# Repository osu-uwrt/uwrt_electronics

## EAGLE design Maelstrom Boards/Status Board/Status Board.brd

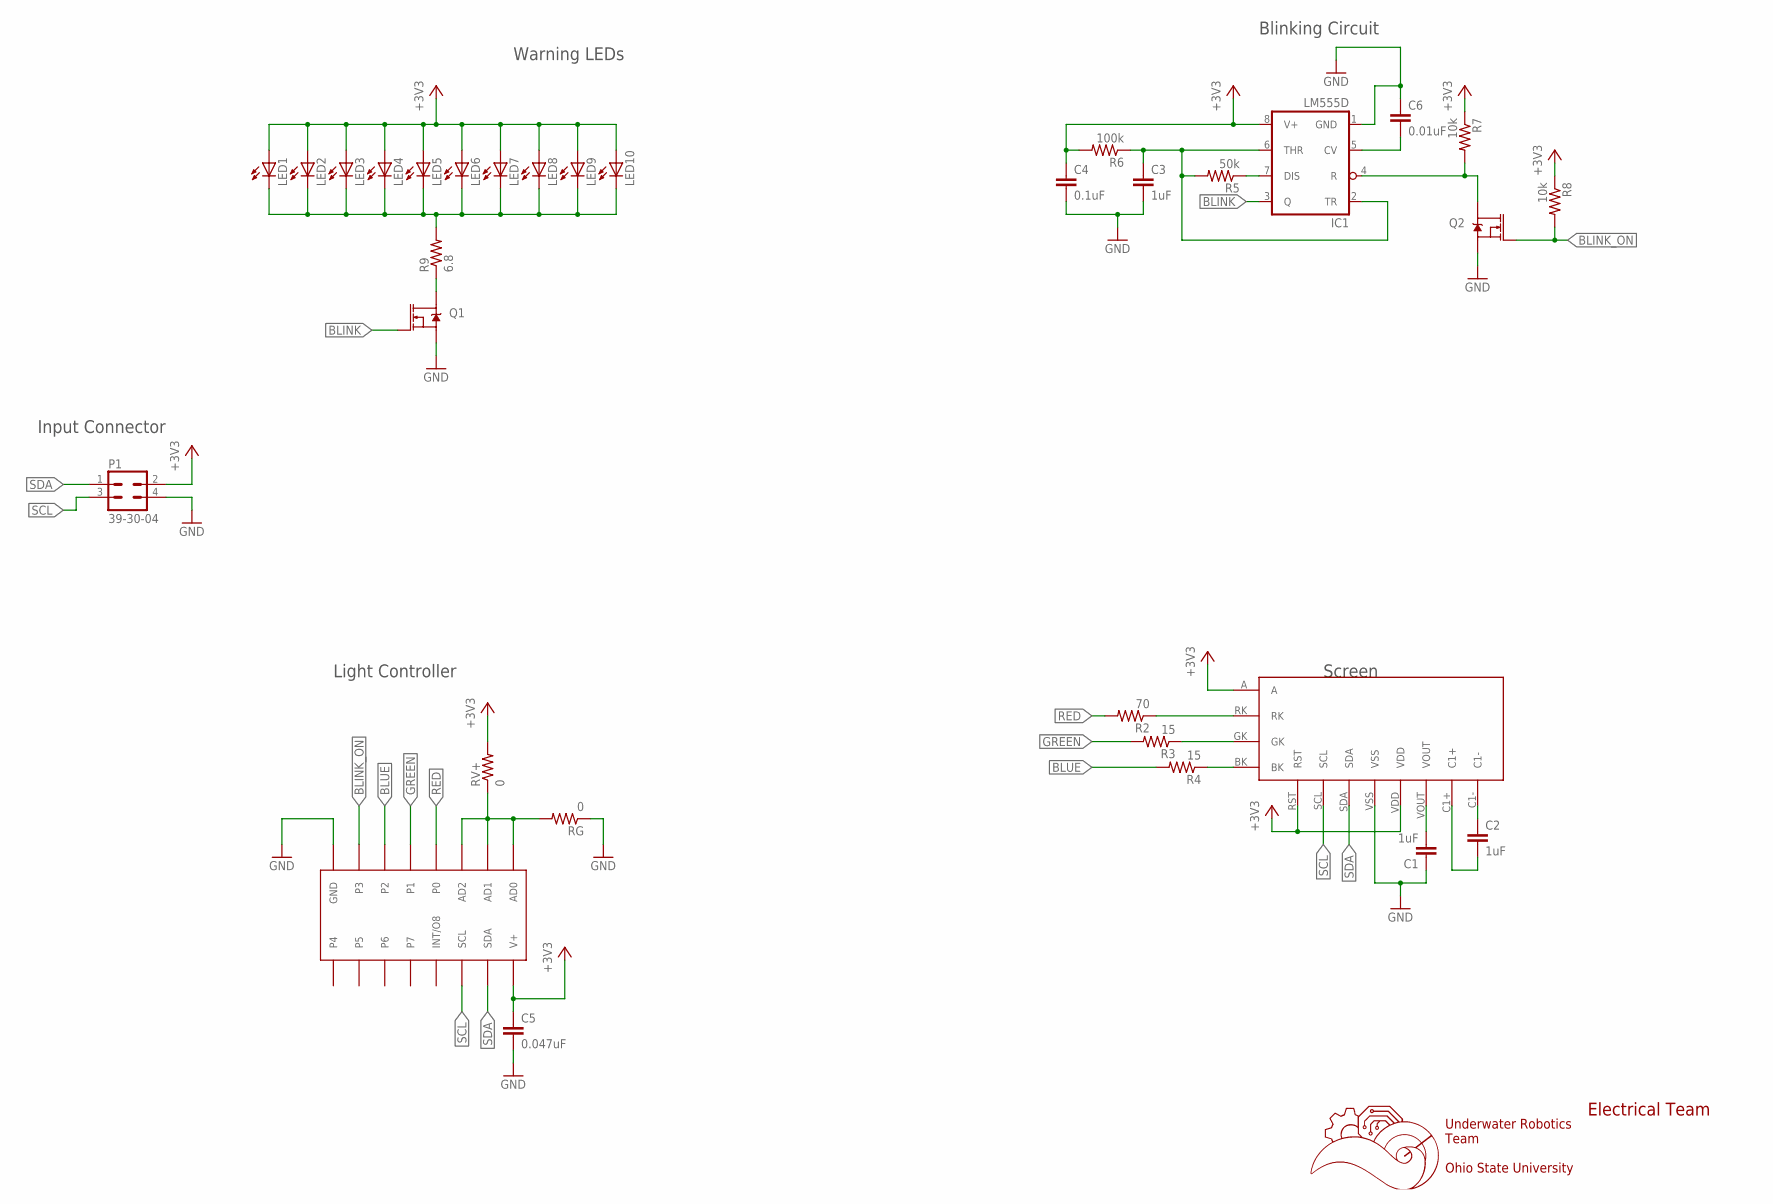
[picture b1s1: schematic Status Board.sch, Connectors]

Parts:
C1, C2, C3: 1uF; C0603
C4: 0.1uF; C0603
C5: 0.047uF; C0603
C6: 0.01uF; C0603
IC1: LM555D; SO08
LED1, LED2, LED3, LED4, LED5, LED6, LED7, LED8, LED9, LED10: LEDCHIPLED_0603; CHIPLED_0603
P1: 39-30-04; 39-30-?04?
Q1, Q2: 310mA/60V/1.6Ω; SOT323
R2: 70; R0603
R3, R4: 15; R0603
R5: 50k; R0603
R6: 100k; R0603
R7, R8: 10k; R0603
R9: 6.8; R0603
RG: 0; R0603
RV+: 0; R0603
U$1: NHD-C0220BIZ
U$2: MAX7315; TSSOP-16

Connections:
+3V3: C4.1, C5.1, IC1.8 (V+), LED1.A, LED2.A, LED3.A, LED4.A, LED5.A, LED6.A, LED7.A, LED8.A, LED9.A, LED10.A, P1.2, R6.2, R7.1, R8.1, RV+.2, U$1.A, U$1.RST, U$1.VDD, U$2.16 (V+)
BLINK: IC1.3 (Q), Q1.1 (G)
BLINK_OFF: IC1.4 (R), Q2.3 (D), R7.2
BLINK_ON: Q2.1 (G), R8.2, U$2.7 (P3)
BLUE: R4.2, U$2.6 (P2)
GND: C1.1, C3.2, C4.2, C5.2, C6.1, IC1.1 (GND), P1.4, Q1.2 (S), Q2.2 (S), RG.1, U$1.VSS, U$2.8 (GND)
GREEN: R3.2, U$2.5 (P1)
unnamed: R3.1, U$1.GK
unnamed: C2.1, U$1.C1-
unnamed: C1.2, U$1.VOUT
unnamed: C2.2, U$1.C1+
unnamed: R4.1, U$1.BK
unnamed: RG.2, RV+.1, U$2.1 (AD0), U$2.2 (AD1), U$2.3 (AD2)
unnamed: R2.1, U$1.RK
unnamed: C6.2, IC1.5 (CV)
unnamed: IC1.7 (DIS), R5.1
unnamed: C3.1, IC1.2 (TR), IC1.6 (THR), R5.2, R6.1
unnamed: Q1.3 (D), R9.1
unnamed: LED1.C, LED2.C, LED3.C, LED4.C, LED5.C, LED6.C, LED7.C, LED8.C, LED9.C, LED10.C, R9.2
RED: R2.2, U$2.4 (P0)
SCL: P1.3, U$1.SCL, U$2.14 (SCL)
SDA: P1.1, U$1.SDA, U$2.15 (SDA)

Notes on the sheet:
Underwater Robotics Team Ohio State University
Electrical Team
Warning LEDs
Blinking Circuit
Screen
Light Controller
Input Connector

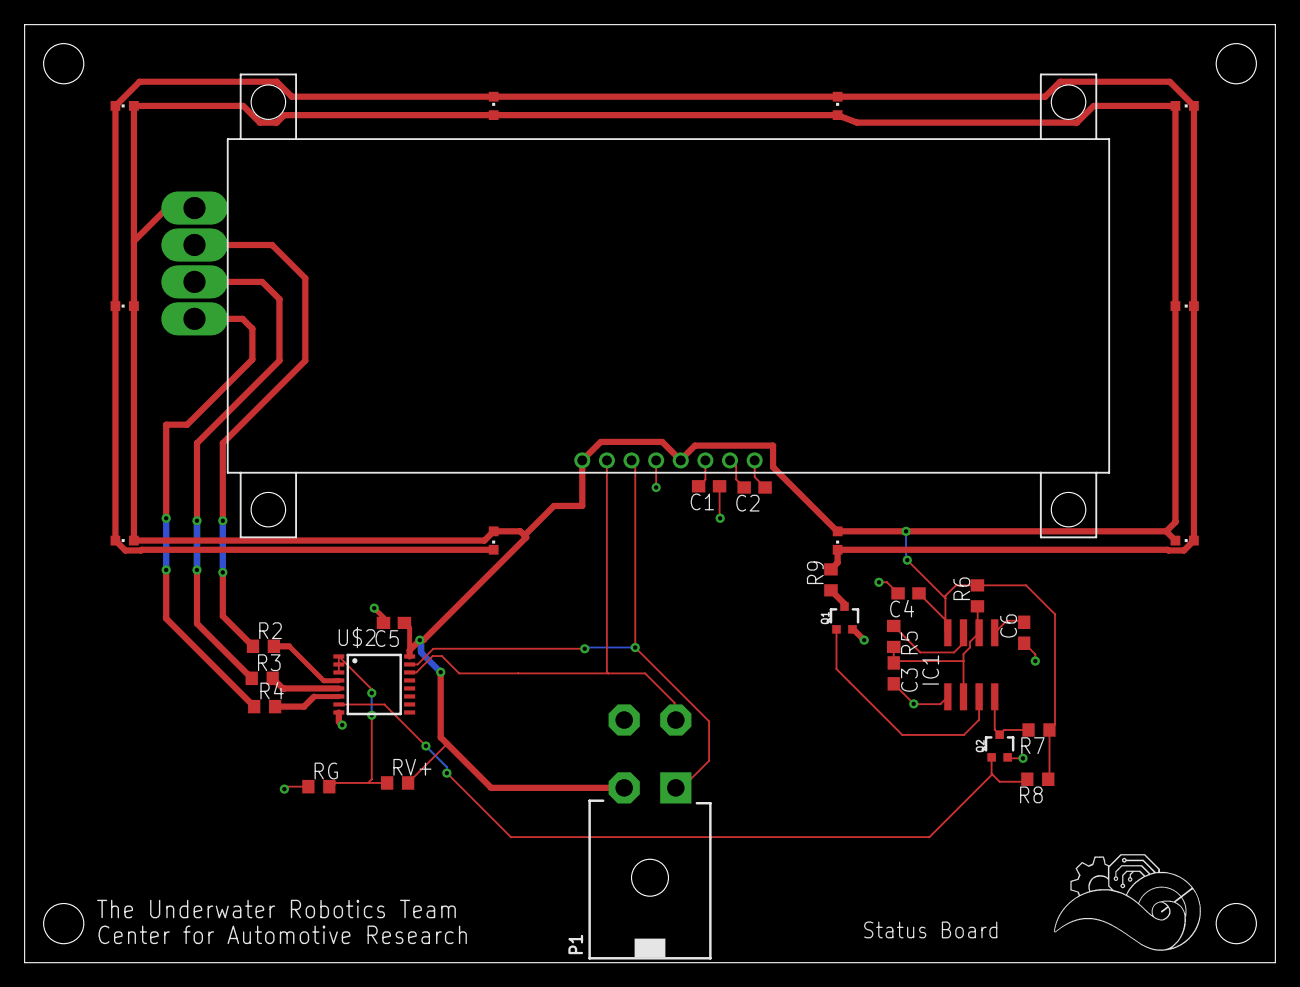
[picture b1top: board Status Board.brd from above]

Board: 2 copper layers, 101.6 x 76.2 mm, 32 parts (0 on the bottom side), 22 nets.

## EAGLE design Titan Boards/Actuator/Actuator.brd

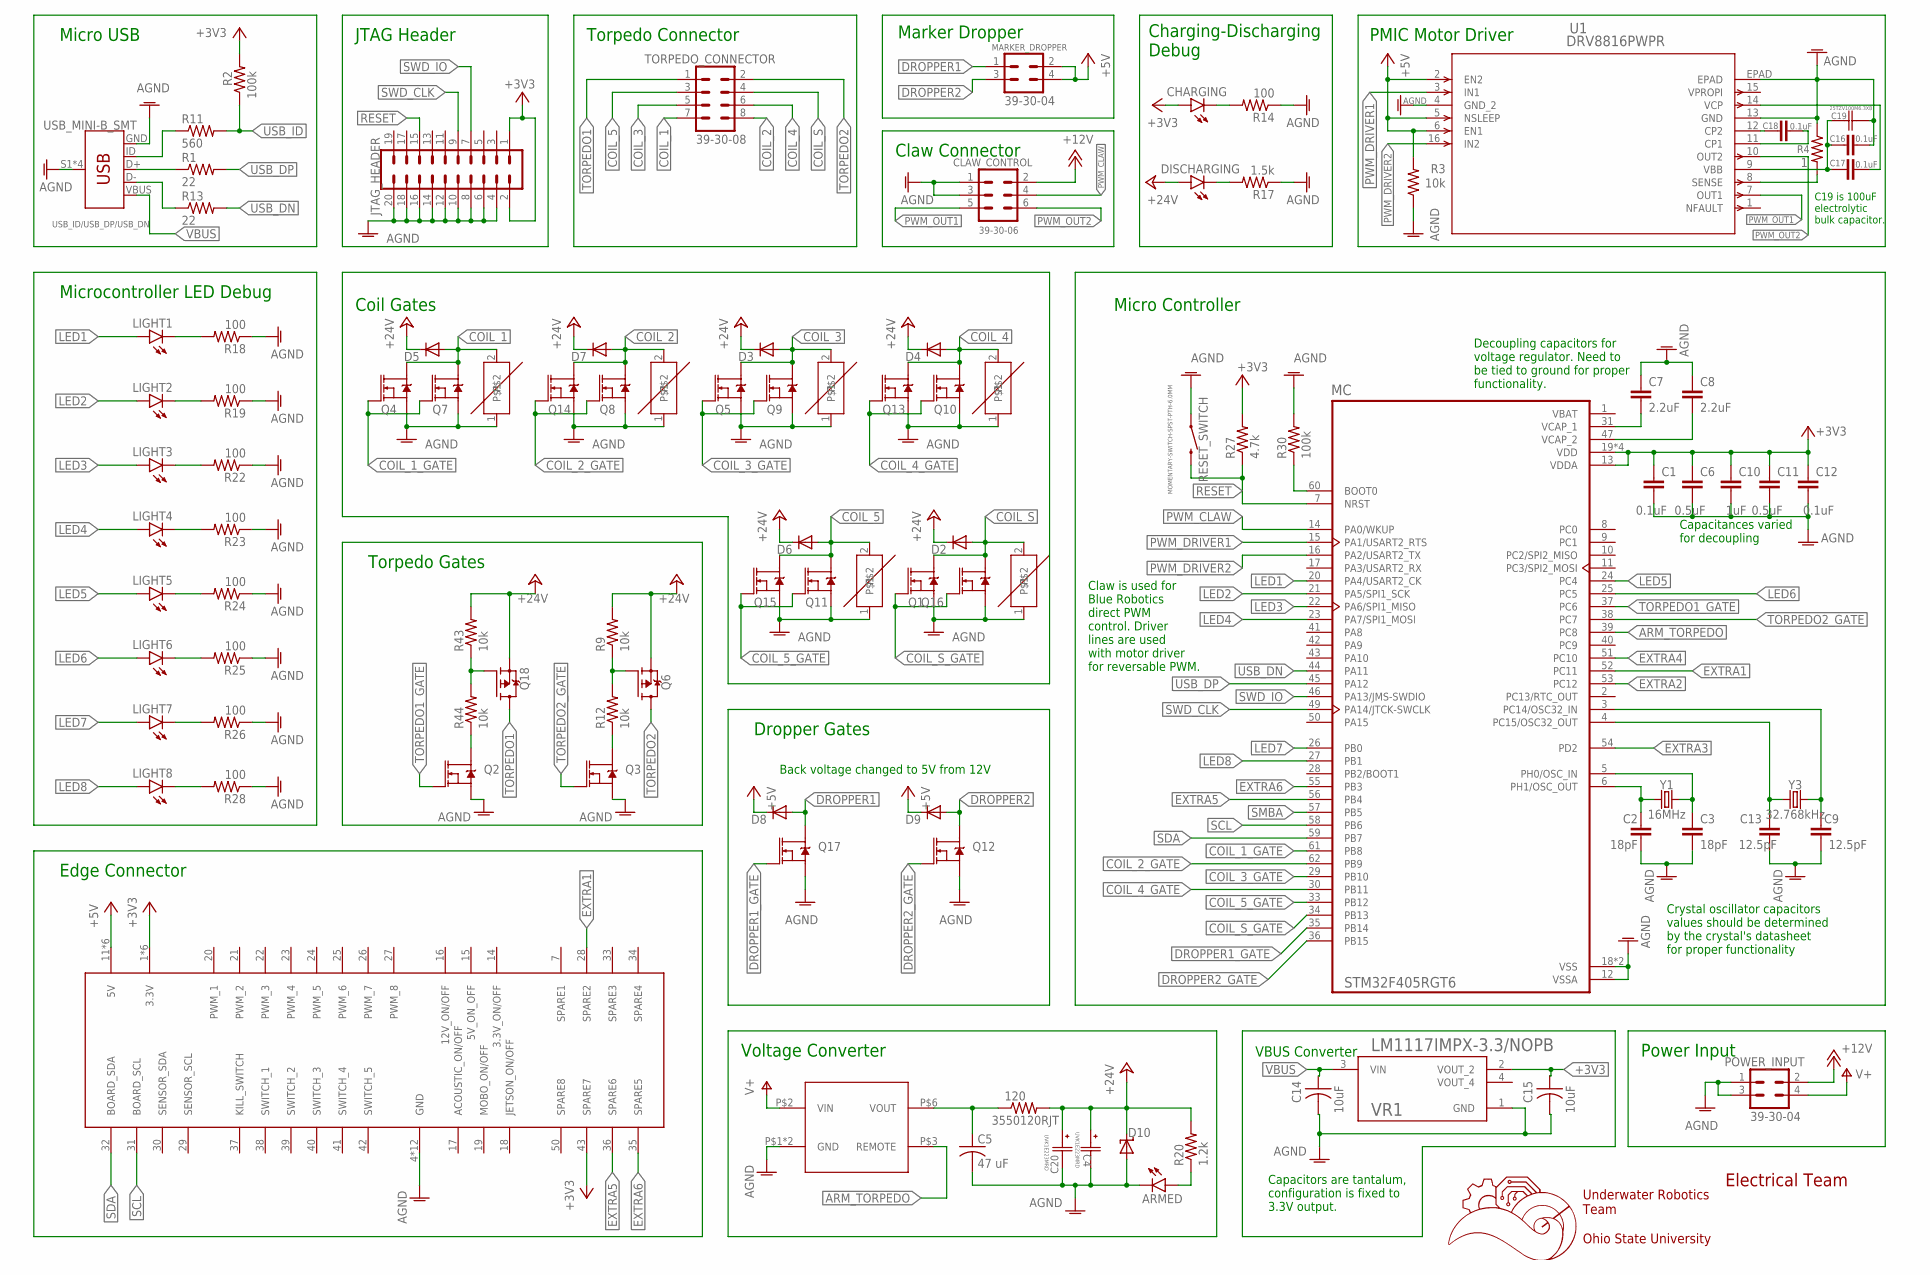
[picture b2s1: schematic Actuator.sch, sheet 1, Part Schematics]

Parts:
120: 3550120RJT
ARMED: LEDCHIPLED_0603; CHIPLED_0603
C1, C12, C16, C17, C18: 0.1uF; C0603
C2, C3: 18pF; C0603
C4, C20: UVK1E223MRD; CAP_UFW_25X50_NCH
C5: 47 uF; C1206K
C6, C11: 0.5uF; C0603
C7, C8: 2.2uF; C0603
C9, C13: 12.5pF; C0603
C10: 1uF; C0603
C14, C15: 10uF; C0603
C19: 25TZV100M6.3X8; CAP_J-V_6P3X8_RUB
CHARGING: LEDCHIPLED_0603; CHIPLED_0603
CLAW_CONTROL: 39-30-06; 39-30-?06?
D2, D3, D4, D5, D6, D7, D8, D9: DIODE-SMB; SMB
D10: SUPPRESSOR-SMBJ; SMBJ
DISCHARGING: LEDCHIPLED_0603; CHIPLED_0603
JTAG_HEADER: CONN_10X2; 2X10
LIGHT1, LIGHT2, LIGHT3, LIGHT4, LIGHT5, LIGHT6, LIGHT7, LIGHT8: LEDCHIPLED_0603; CHIPLED_0603
MARKER_DROPPER: 39-30-04; 39-30-?04?
MC: STM32F405RGT6; QFP50P1200X1200X160-64N
POWER_INPUT: 39-30-04; 39-30-?04?
Q1, Q2, Q3, Q4, Q5, Q7, Q8, Q9, Q10, Q11, Q12, Q13, Q14, Q15, Q16, Q17: MOSFET-NCH-AO3404A; SOT23-3
Q6, Q18: FDD4141TO252; TO252
R1, R13: 22; R0603
R2, R30: 100k; R0603
R3, R9, R12, R43, R44: 10k; R0603
R4: 1; R0805
R11: 560; R0603
R14, R18, R19, R22, R23, R24, R25, R26, R28: 100; R0805
R17: 1.5k; R0805
R20: 1.2k; R0805
R27: 4.7k; R0603
RESET_SWITCH: MOMENTARY-SWITCH-SPST-PTH-6.0MM; TACTILE_SWITCH_PTH_6.0MM
TORPEDO_CONNECTOR: 39-30-08; 39-30-?08?
U1: DRV8816PWPR; PWP_16
U$1: 5530843-EDGE; 5530843-6-BOARDFINGERS
U$2, U$3, U$4, U$5, U$7, U$8: ERZ-VF2M270ERZ-VF2M270; RESM8060X320N
U$6: TMR6-2415
USB_ID/USB_DP/USB_DN: USB_MINI-B_SMT; USB-MINIB
VR1: LM1117IMPX-3.3/NOPB; VREG_LM1117IMPX-3.3/NOPB
Y1: 16MHz; HC49US
Y3: 32.768kHz; CRYSTAL-SMD-3.2X1.5MM

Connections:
+3V3: C1.1, C6.1, C10.1, C11.1, C12.1, C15.1, CHARGING.A, JTAG_HEADER.1, JTAG_HEADER.2, MC.13 (VDDA), MC.19 (VDD), MC.32 (VDD), MC.48 (VDD), MC.64 (VDD), R2.2, R27.2, U$1.1 (3.3V), U$1.2 (3.3V), U$1.3 (3.3V), U$1.43 (SPARE7), U$1.54 (3.3V), U$1.55 (3.3V), U$1.56 (3.3V), VR1.2 (VOUT_2)
+5V: D8.C, D9.C, MARKER_DROPPER.2, MARKER_DROPPER.4, R3.2, U1.2 (EN2), U1.5 (NSLEEP), U1.6 (EN1), U$1.11 (5V), U$1.12 (5V), U$1.13 (5V), U$1.44 (5V), U$1.45 (5V), U$1.46 (5V)
+12V: CLAW_CONTROL.2, POWER_INPUT.2
+24V: 120.P$2 (2), C4.1, C20.1, D2.C, D3.C, D4.C, D5.C, D6.C, D7.C, D10.C, DISCHARGING.A, Q6.2 (S), Q18.2 (S), R9.2, R20.2, R43.2
AGND: ARMED.C, C1.2, C2.2, C3.2, C4.2, C5.2, C6.2, C7.1, C8.1, C9.2, C10.2, C11.2, C12.2, C13.2, C14.2, C15.2, C16.2, C19.2, C20.2, CLAW_CONTROL.1, CLAW_CONTROL.3, D10.A, JTAG_HEADER.4, JTAG_HEADER.6, JTAG_HEADER.8, JTAG_HEADER.10, JTAG_HEADER.12, JTAG_HEADER.14, JTAG_HEADER.16, JTAG_HEADER.18, JTAG_HEADER.20, MC.12 (VSSA), MC.18 (VSS), MC.63 (VSS), POWER_INPUT.1, POWER_INPUT.3, Q1.2 (S), Q2.2 (S), Q3.2 (S), Q4.2 (S), Q5.2 (S), Q7.2 (S), Q8.2 (S), Q9.2 (S), Q10.2 (S), Q11.2 (S), Q12.2 (S), Q13.2 (S), Q14.2 (S), Q15.2 (S), Q16.2 (S), Q17.2 (S), R3.1, R4.1, R14.1, R17.1, R18.1, R19.1, R22.1, R23.1, R24.1, R25.1, R26.1, R28.1, R30.2, RESET_SWITCH.1, U1.4 (GND_2), U1.13 (GND), U1.EPAD, U$1.4 (GND), U$1.5 (GND), U$1.6 (GND), U$1.8 (GND), U$1.9 (GND), U$1.10 (GND), U$1.47 (GND), U$1.48 (GND), U$1.49 (GND), U$1.51 (GND), U$1.52 (GND), U$1.53 (GND), U$2.1, U$3.1, U$4.1, U$5.1, U$6.P$1 (GND), U$6.P$7 (GND), U$7.1, U$8.1, USB_ID/USB_DP/USB_DN.GND, USB_ID/USB_DP/USB_DN.S1 (SHIELD), USB_ID/USB_DP/USB_DN.S2 (SHIELD), USB_ID/USB_DP/USB_DN.S3 (SHIELD), USB_ID/USB_DP/USB_DN.S4 (SHIELD), VR1.1 (GND)
ARM_TORPEDO: MC.39 (PC8), U$6.P$3 (REMOTE)
COIL_1: D5.A, Q4.3 (D), Q7.3 (D), TORPEDO_CONNECTOR.7, U$8.2
COIL_1_GATE: MC.61 (PB8), Q4.1 (G), Q7.1 (G)
COIL_2: D7.A, Q8.3 (D), Q14.3 (D), TORPEDO_CONNECTOR.8, U$7.2
COIL_2_GATE: MC.62 (PB9), Q8.1 (G), Q14.1 (G)
COIL_3: D3.A, Q5.3 (D), Q9.3 (D), TORPEDO_CONNECTOR.5, U$5.2
COIL_3_GATE: MC.29 (PB10), Q5.1 (G), Q9.1 (G)
COIL_4: D4.A, Q10.3 (D), Q13.3 (D), TORPEDO_CONNECTOR.6, U$4.2
COIL_4_GATE: MC.30 (PB11), Q10.1 (G), Q13.1 (G)
COIL_5: D6.A, Q11.3 (D), Q15.3 (D), TORPEDO_CONNECTOR.3, U$3.2
COIL_5_GATE: MC.33 (PB12), Q11.1 (G), Q15.1 (G)
COIL_S: D2.A, Q1.3 (D), Q16.3 (D), TORPEDO_CONNECTOR.4, U$2.2
COIL_S_GATE: MC.34 (PB13), Q1.1 (G), Q16.1 (G)
DROPPER1: D8.A, MARKER_DROPPER.1, Q17.3 (D)
DROPPER1_GATE: MC.35 (PB14), Q17.1 (G)
DROPPER2: D9.A, MARKER_DROPPER.3, Q12.3 (D)
DROPPER2_GATE: MC.36 (PB15), Q12.1 (G)
EXTRA1: MC.52 (PC11), U$1.28 (SPARE2)
EXTRA2: MC.53 (PC12)
EXTRA3: MC.54 (PD2)
EXTRA4: MC.51 (PC10)
EXTRA5: MC.56 (PB4), U$1.36 (SPARE6)
EXTRA6: MC.55 (PB3), U$1.35 (SPARE5)
LED1: LIGHT1.A, MC.20 (PA4/USART2_CK)
LED2: LIGHT2.A, MC.21 (PA5/SPI1_SCK)
LED3: LIGHT3.A, MC.22 (PA6/SPI1_MISO)
LED4: LIGHT4.A, MC.23 (PA7/SPI1_MOSI)
LED5: LIGHT5.A, MC.24 (PC4)
LED6: LIGHT6.A, MC.25 (PC5)
LED7: LIGHT7.A, MC.26 (PB0)
LED8: LIGHT8.A, MC.27 (PB1)
unnamed: C2.1, MC.6 (PH1/OSC_OUT), Y1.1
unnamed: C3.1, MC.5 (PH0/OSC_IN), Y1.2
unnamed: CHARGING.C, R14.2
unnamed: C8.2, MC.47 (VCAP_2)
unnamed: R11.1, USB_ID/USB_DP/USB_DN.ID
unnamed: R1.1, USB_ID/USB_DP/USB_DN.D+
unnamed: R13.1, USB_ID/USB_DP/USB_DN.D-
unnamed: ARMED.A, R20.1
unnamed: C7.2, MC.31 (VCAP_1)
unnamed: C13.1, MC.4 (PC15/OSC32_OUT), Y3.P$2 (2)
unnamed: DISCHARGING.C, R17.2
unnamed: LIGHT1.C, R18.2
unnamed: LIGHT2.C, R19.2
unnamed: LIGHT3.C, R22.2
unnamed: LIGHT4.C, R23.2
unnamed: LIGHT5.C, R24.2
unnamed: LIGHT6.C, R25.2
unnamed: LIGHT7.C, R26.2
unnamed: LIGHT8.C, R28.2
unnamed: 120.P$1 (1), C5.1, U$6.P$6 (VOUT)
unnamed: C9.1, MC.3 (PC14/OSC32_IN), Y3.P$1 (1)
unnamed: MC.60 (BOOT0), R30.1
unnamed: Q18.1 (G), R43.1, R44.2
unnamed: Q2.3 (D), R44.1
unnamed: Q6.1 (G), R9.1, R12.2
unnamed: Q3.3 (D), R12.1
unnamed: R4.2, U1.8 (SENSE)
unnamed: C17.2, U1.14 (VCP)
unnamed: C16.1, C17.1, C19.1, U1.9 (VBB)
unnamed: C18.2, U1.11 (CP1)
unnamed: C18.1, U1.12 (CP2)
PWM_CLAW: CLAW_CONTROL.4, MC.14 (PA0/WKUP)
PWM_DRIVER1: MC.15 (PA1/USART2_RTS), U1.3 (IN1)
PWM_DRIVER2: MC.16 (PA2/USART2_TX), U1.16 (IN2)
PWM_OUT1: CLAW_CONTROL.5, U1.7 (OUT1)
PWM_OUT2: CLAW_CONTROL.6, U1.10 (OUT2)
RESET: JTAG_HEADER.15, MC.7 (NRST), R27.1, RESET_SWITCH.3 (2)
SCL: MC.58 (PB6), U$1.31 (BOARD_SCL)
SDA: MC.59 (PB7), U$1.32 (BOARD_SDA)
SMBA: MC.57 (PB5)
SWD_CLK: JTAG_HEADER.9, MC.49 (PA14/JTCK-SWCLK)
SWD_IO: JTAG_HEADER.7, MC.46 (PA13/JMS-SWDIO)
TORPEDO1: Q18.3 (D), TORPEDO_CONNECTOR.1
TORPEDO1_GATE: MC.37 (PC6), Q2.1 (G)
TORPEDO2: Q6.3 (D), TORPEDO_CONNECTOR.2
TORPEDO2_GATE: MC.38 (PC7), Q3.1 (G)
USB_DN: MC.44 (PA11), R13.2
USB_DP: MC.45 (PA12), R1.2
USB_ID: R2.1, R11.2
V+: POWER_INPUT.4, U$6.P$2 (VIN)
VBAT: MC.1 (VBAT)
VBUS: C14.1, USB_ID/USB_DP/USB_DN.VBUS, VR1.3 (VIN)

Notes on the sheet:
Underwater Robotics Team Ohio State University
Electrical Team
Micro USB
JTAG Header
Torpedo Connector
Claw Connector
Charging-Discharging Debug
Microcontroller LED Debug
Edge Connector
Voltage Converter
Decoupling capacitors for voltage regulator. Need to be tied to ground for proper functionality.
Crystal oscillator capacitors values should be determined by the crystal's datasheet for proper functionality
Dropper Gates
Coil Gates
Torpedo Gates
Marker Dropper
Power Input
Micro Controller
Back voltage changed to 5V from 12V
Capacitances varied for decoupling
Capacitors are tantalum, configuration is fixed to 3.3V output.
VBUS Converter
PMIC Motor Driver
Claw is used for Blue Robotics direct PWM control. Driver lines are used with motor driver for reversable PWM.
C19 is 100uF electrolytic bulk capacitor.

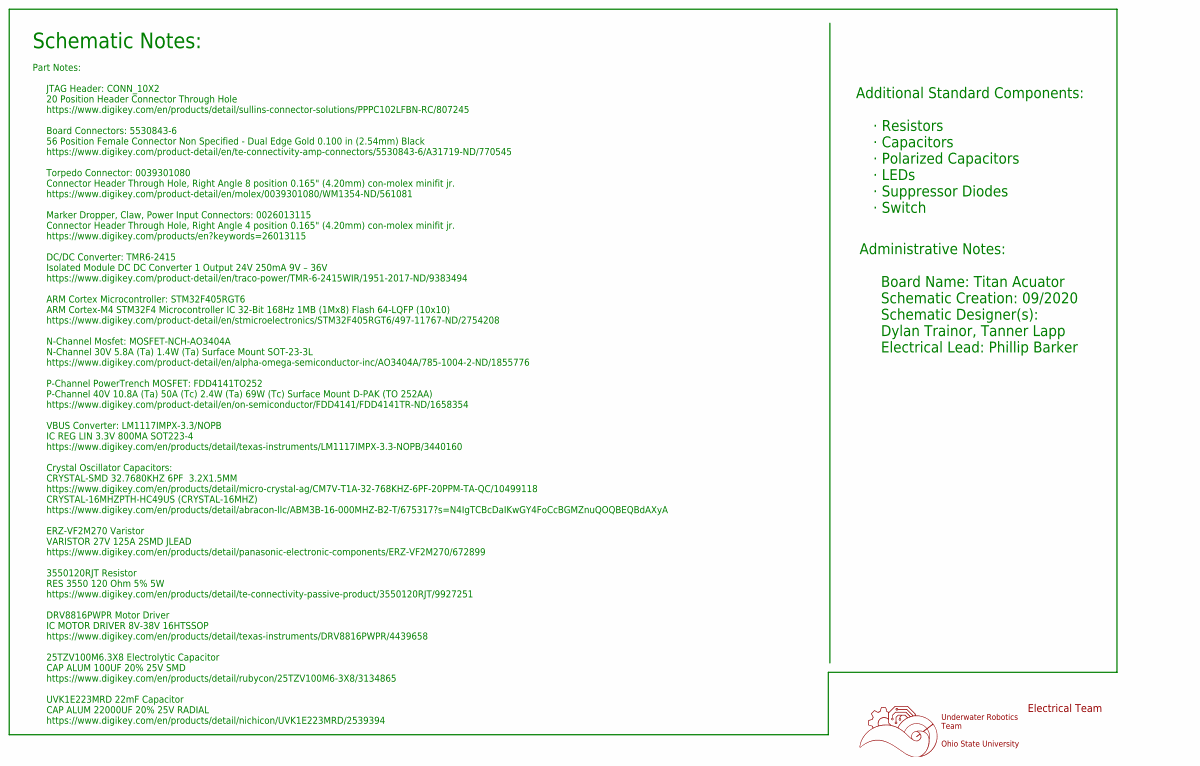
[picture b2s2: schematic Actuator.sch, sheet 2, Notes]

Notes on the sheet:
Underwater Robotics Team Ohio State University
Electrical Team
Schematic Notes:
Part Notes: JTAG Header: CONN_10X2 20 Position Header Connector Through Hole https://www.digikey.com/en/products/detail/sullins-connector-solutions/PPPC102LFBN-RC/807245 Board Connectors: 5530843-6 56 Position Female Connector Non Specified - Dual Edge Gold 0.100 in (2.54mm) Black https://www.digik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
Administrative Notes: Board Name: Titan Acuator Schematic Creation: 09/2020 Schematic Designer(s): Dylan Trainor, Tanner Lapp Electrical Lead: Phillip Barker
Additional Standard Components: · Resistors · Capacitors · Polarized Capacitors · LEDs · Suppressor Diodes · Switch

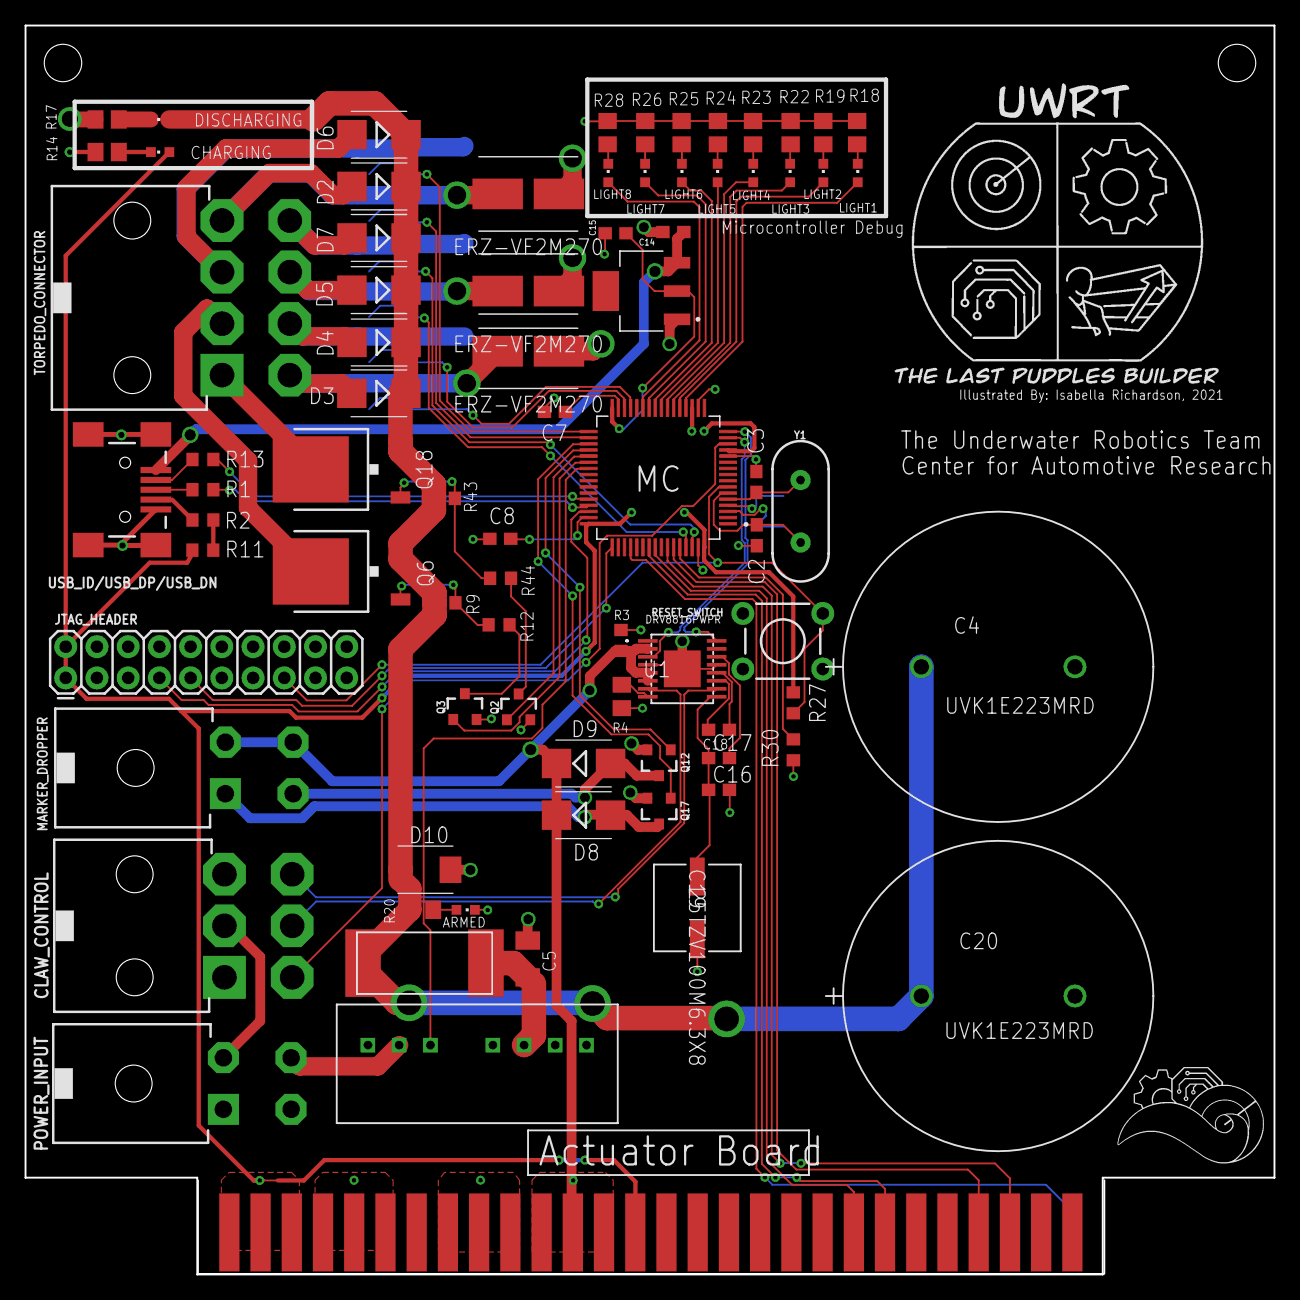
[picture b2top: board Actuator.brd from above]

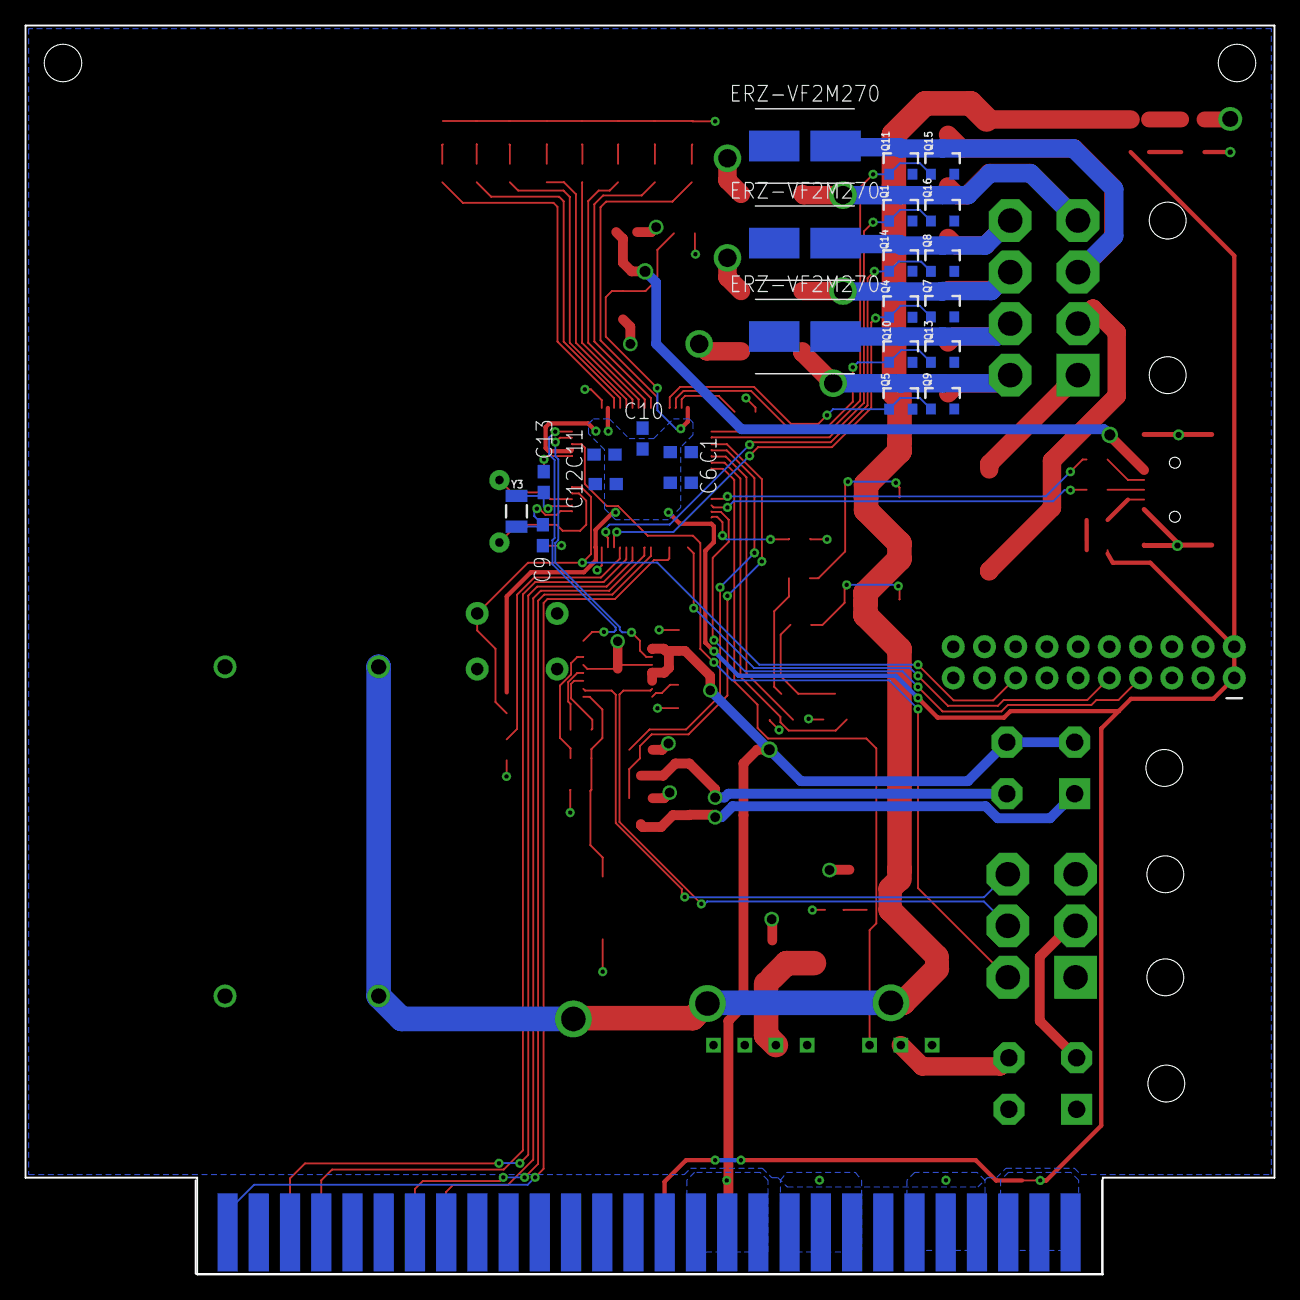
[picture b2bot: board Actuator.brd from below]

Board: 2 copper layers, 101.6 x 101.6 mm, 102 parts (23 on the bottom side), 83 nets.

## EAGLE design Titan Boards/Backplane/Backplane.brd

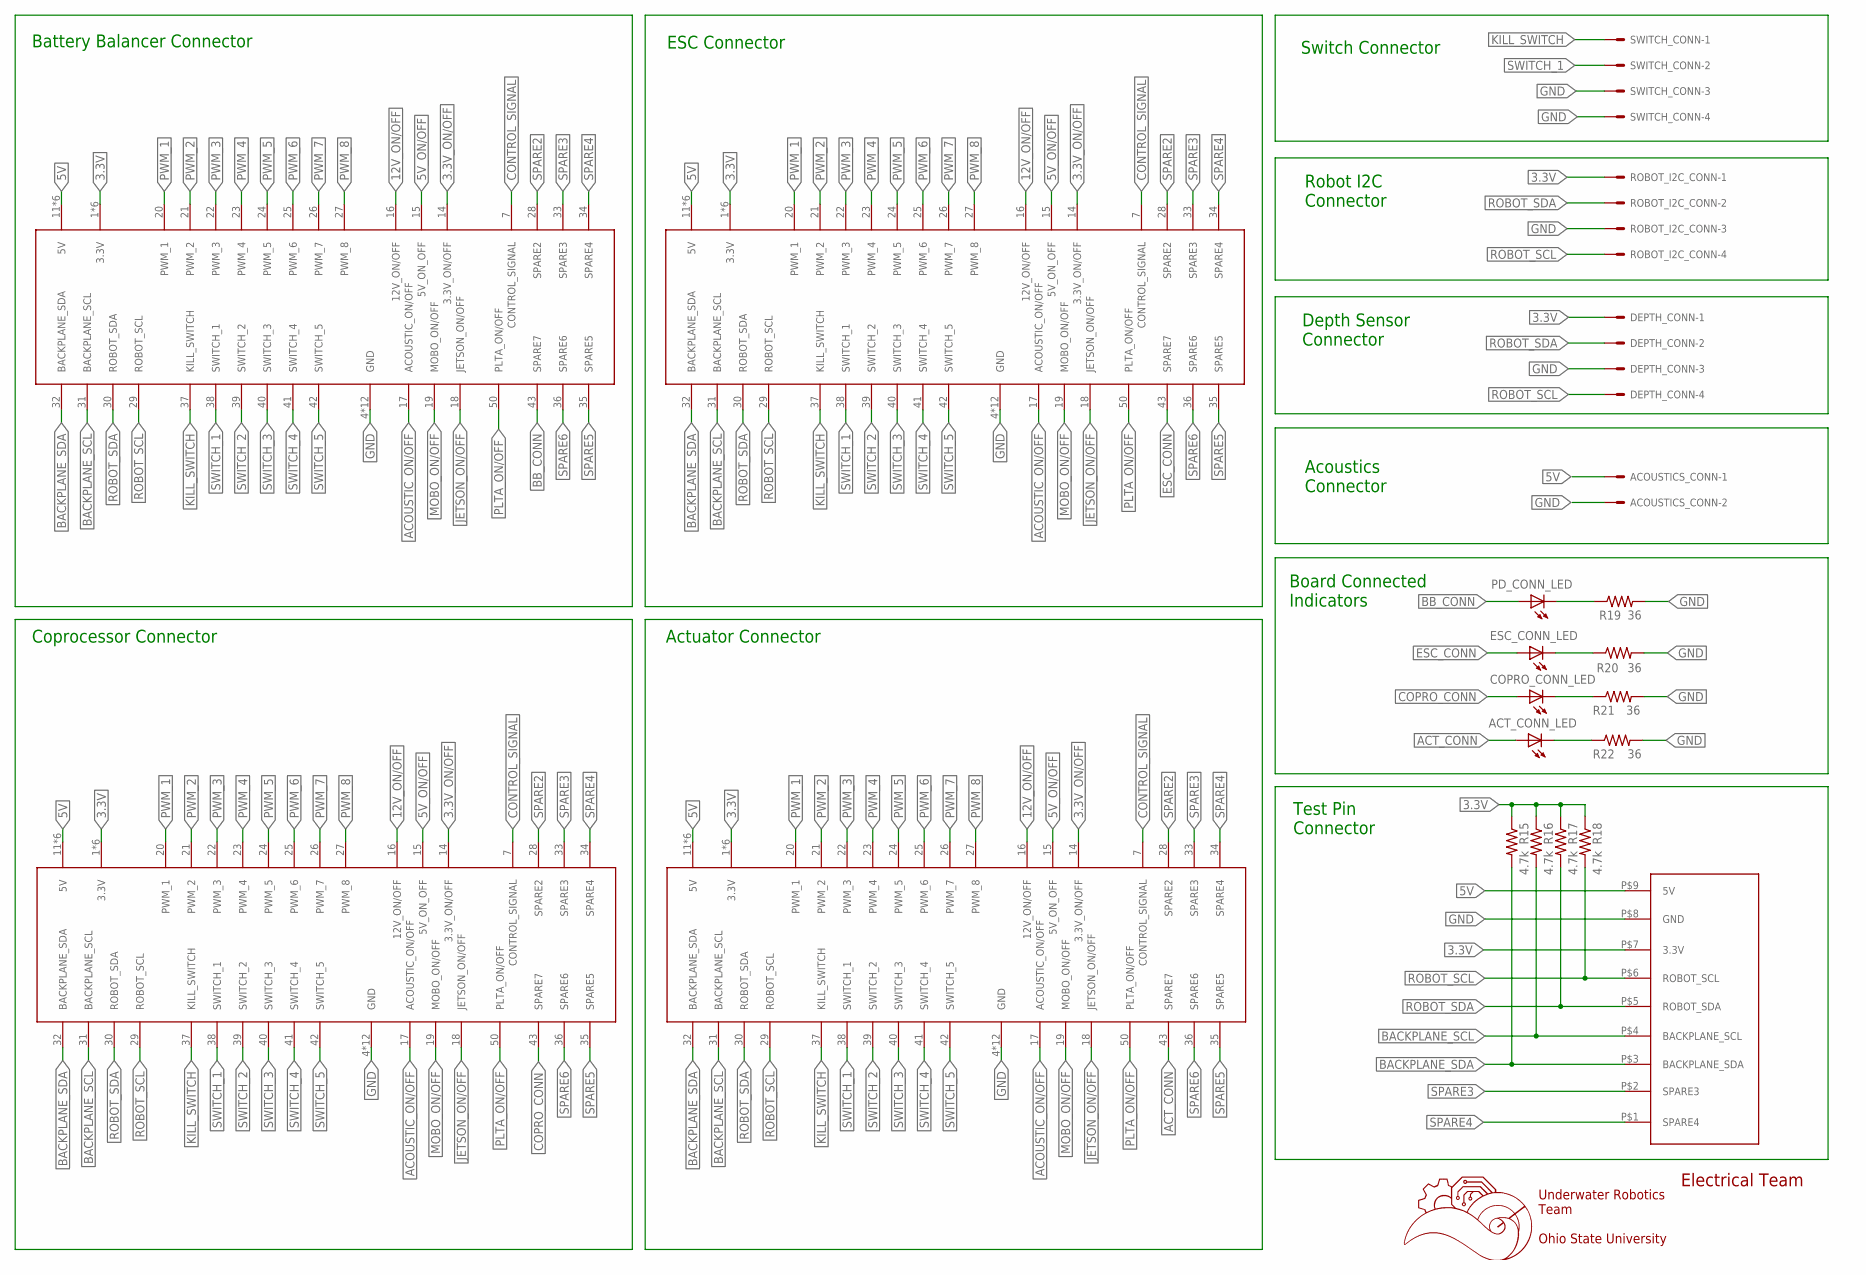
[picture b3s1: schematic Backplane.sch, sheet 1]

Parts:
ACOUSTICS_CONN: 555X-2V; 5566-2
ACT_CONN_LED: LEDCHIP-LED0603; CHIP-LED0603
COPRO_CONN_LED: LEDCHIP-LED0603; CHIP-LED0603
DEPTH_CONN: 555X-4V; 5566-4
ESC_CONN_LED: LEDCHIP-LED0603; CHIP-LED0603
PD_CONN_LED: LEDCHIP-LED0603; CHIP-LED0603
R15, R16, R17, R18: 4.7k; R0603
R19, R20, R21, R22: 36; R0603
ROBOT_I2C_CONN: 555X-4V; 5566-4
SWITCH_CONN: 555X-4V; 5566-4
TESTPIN_CONNECTOR: 929870-01-09_4; 929852-01-09_1ROW
U$1, U$2, U$3, U$4: 5530843-FEMALE; 5530843-6-BACKPLANEMATE

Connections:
3.3V: DEPTH_CONN.1, R15.1, R16.1, R17.1, R18.1, ROBOT_I2C_CONN.1, TESTPIN_CONNECTOR.P$7 (3.3V), U$1.1 (3.3V), U$1.2 (3.3V), U$1.3 (3.3V), U$1.54 (3.3V), U$1.55 (3.3V), U$1.56 (3.3V), U$2.1 (3.3V), U$2.2 (3.3V), U$2.3 (3.3V), U$2.54 (3.3V), U$2.55 (3.3V), U$2.56 (3.3V), U$3.1 (3.3V), U$3.2 (3.3V), U$3.3 (3.3V), U$3.54 (3.3V), U$3.55 (3.3V), U$3.56 (3.3V), U$4.1 (3.3V), U$4.2 (3.3V), U$4.3 (3.3V), U$4.54 (3.3V), U$4.55 (3.3V), U$4.56 (3.3V)
3.3V_ON/OFF: U$1.14 (3.3V_ON/OFF), U$2.14 (3.3V_ON/OFF), U$3.14 (3.3V_ON/OFF), U$4.14 (3.3V_ON/OFF)
5V: ACOUSTICS_CONN.1, TESTPIN_CONNECTOR.P$9 (5V), U$1.11 (5V), U$1.12 (5V), U$1.13 (5V), U$1.44 (5V), U$1.45 (5V), U$1.46 (5V), U$2.11 (5V), U$2.12 (5V), U$2.13 (5V), U$2.44 (5V), U$2.45 (5V), U$2.46 (5V), U$3.11 (5V), U$3.12 (5V), U$3.13 (5V), U$3.44 (5V), U$3.45 (5V), U$3.46 (5V), U$4.11 (5V), U$4.12 (5V), U$4.13 (5V), U$4.44 (5V), U$4.45 (5V), U$4.46 (5V)
5V_ON/OFF: U$1.15 (5V_ON_OFF), U$2.15 (5V_ON_OFF), U$3.15 (5V_ON_OFF), U$4.15 (5V_ON_OFF)
12V_ON/OFF: U$1.16 (12V_ON/OFF), U$2.16 (12V_ON/OFF), U$3.16 (12V_ON/OFF), U$4.16 (12V_ON/OFF)
ACOUSTIC_ON/OFF: U$1.17 (ACOUSTIC_ON/OFF), U$2.17 (ACOUSTIC_ON/OFF), U$3.17 (ACOUSTIC_ON/OFF), U$4.17 (ACOUSTIC_ON/OFF)
ACT_CONN: ACT_CONN_LED.A, U$4.43 (SPARE7)
BACKPLANE_SCL: R16.2, TESTPIN_CONNECTOR.P$4 (BACKPLANE_SCL), U$1.31 (BACKPLANE_SCL), U$2.31 (BACKPLANE_SCL), U$3.31 (BACKPLANE_SCL), U$4.31 (BACKPLANE_SCL)
BACKPLANE_SDA: R15.2, TESTPIN_CONNECTOR.P$3 (BACKPLANE_SDA), U$1.32 (BACKPLANE_SDA), U$2.32 (BACKPLANE_SDA), U$3.32 (BACKPLANE_SDA), U$4.32 (BACKPLANE_SDA)
BB_CONN: PD_CONN_LED.A, U$1.43 (SPARE7)
CONTROL_SIGNAL: U$1.7 (CONTROL_SIGNAL), U$2.7 (CONTROL_SIGNAL), U$3.7 (CONTROL_SIGNAL), U$4.7 (CONTROL_SIGNAL)
COPRO_CONN: COPRO_CONN_LED.A, U$3.43 (SPARE7)
ESC_CONN: ESC_CONN_LED.A, U$2.43 (SPARE7)
GND: ACOUSTICS_CONN.2, DEPTH_CONN.3, R19.2, R20.2, R21.2, R22.2, ROBOT_I2C_CONN.3, SWITCH_CONN.3, SWITCH_CONN.4, TESTPIN_CONNECTOR.P$8 (GND), U$1.4 (GND), U$1.5 (GND), U$1.6 (GND), U$1.8 (GND), U$1.9 (GND), U$1.10 (GND), U$1.47 (GND), U$1.48 (GND), U$1.49 (GND), U$1.51 (GND), U$1.52 (GND), U$1.53 (GND), U$2.4 (GND), U$2.5 (GND), U$2.6 (GND), U$2.8 (GND), U$2.9 (GND), U$2.10 (GND), U$2.47 (GND), U$2.48 (GND), U$2.49 (GND), U$2.51 (GND), U$2.52 (GND), U$2.53 (GND), U$3.4 (GND), U$3.5 (GND), U$3.6 (GND), U$3.8 (GND), U$3.9 (GND), U$3.10 (GND), U$3.47 (GND), U$3.48 (GND), U$3.49 (GND), U$3.51 (GND), U$3.52 (GND), U$3.53 (GND), U$4.4 (GND), U$4.5 (GND), U$4.6 (GND), U$4.8 (GND), U$4.9 (GND), U$4.10 (GND), U$4.47 (GND), U$4.48 (GND), U$4.49 (GND), U$4.51 (GND), U$4.52 (GND), U$4.53 (GND)
JETSON_ON/OFF: U$1.18 (JETSON_ON/OFF), U$2.18 (JETSON_ON/OFF), U$3.18 (JETSON_ON/OFF), U$4.18 (JETSON_ON/OFF)
KILL_SWITCH: SWITCH_CONN.1, U$1.37 (KILL_SWITCH), U$2.37 (KILL_SWITCH), U$3.37 (KILL_SWITCH), U$4.37 (KILL_SWITCH)
MOBO_ON/OFF: U$1.19 (MOBO_ON/OFF), U$2.19 (MOBO_ON/OFF), U$3.19 (MOBO_ON/OFF), U$4.19 (MOBO_ON/OFF)
unnamed: PD_CONN_LED.C, R19.1
unnamed: ESC_CONN_LED.C, R20.1
unnamed: COPRO_CONN_LED.C, R21.1
unnamed: ACT_CONN_LED.C, R22.1
PLTA_ON/OFF: U$1.50 (PLTA_ON/OFF), U$2.50 (PLTA_ON/OFF), U$3.50 (PLTA_ON/OFF), U$4.50 (PLTA_ON/OFF)
PWM_1: U$1.20 (PWM_1), U$2.20 (PWM_1), U$3.20 (PWM_1), U$4.20 (PWM_1)
PWM_2: U$1.21 (PWM_2), U$2.21 (PWM_2), U$3.21 (PWM_2), U$4.21 (PWM_2)
PWM_3: U$1.22 (PWM_3), U$2.22 (PWM_3), U$3.22 (PWM_3), U$4.22 (PWM_3)
PWM_4: U$1.23 (PWM_4), U$2.23 (PWM_4), U$3.23 (PWM_4), U$4.23 (PWM_4)
PWM_5: U$1.24 (PWM_5), U$2.24 (PWM_5), U$3.24 (PWM_5), U$4.24 (PWM_5)
PWM_6: U$1.25 (PWM_6), U$2.25 (PWM_6), U$3.25 (PWM_6), U$4.25 (PWM_6)
PWM_7: U$1.26 (PWM_7), U$2.26 (PWM_7), U$3.26 (PWM_7), U$4.26 (PWM_7)
PWM_8: U$1.27 (PWM_8), U$2.27 (PWM_8), U$3.27 (PWM_8), U$4.27 (PWM_8)
ROBOT_SCL: DEPTH_CONN.4, R18.2, ROBOT_I2C_CONN.4, TESTPIN_CONNECTOR.P$6 (ROBOT_SCL), U$1.29 (ROBOT_SCL), U$2.29 (ROBOT_SCL), U$3.29 (ROBOT_SCL), U$4.29 (ROBOT_SCL)
ROBOT_SDA: DEPTH_CONN.2, R17.2, ROBOT_I2C_CONN.2, TESTPIN_CONNECTOR.P$5 (ROBOT_SDA), U$1.30 (ROBOT_SDA), U$2.30 (ROBOT_SDA), U$3.30 (ROBOT_SDA), U$4.30 (ROBOT_SDA)
SPARE2: U$1.28 (SPARE2), U$2.28 (SPARE2), U$3.28 (SPARE2), U$4.28 (SPARE2)
SPARE3: TESTPIN_CONNECTOR.P$2 (SPARE3), U$1.33 (SPARE3), U$2.33 (SPARE3), U$3.33 (SPARE3), U$4.33 (SPARE3)
SPARE4: TESTPIN_CONNECTOR.P$1 (SPARE4), U$1.34 (SPARE4), U$2.34 (SPARE4), U$3.34 (SPARE4), U$4.34 (SPARE4)
SPARE5: U$1.35 (SPARE5), U$2.35 (SPARE5), U$3.35 (SPARE5), U$4.35 (SPARE5)
SPARE6: U$1.36 (SPARE6), U$2.36 (SPARE6), U$3.36 (SPARE6), U$4.36 (SPARE6)
SWITCH_1: SWITCH_CONN.2, U$1.38 (SWITCH_1), U$2.38 (SWITCH_1), U$3.38 (SWITCH_1), U$4.38 (SWITCH_1)
SWITCH_2: U$1.39 (SWITCH_2), U$2.39 (SWITCH_2), U$3.39 (SWITCH_2), U$4.39 (SWITCH_2)
SWITCH_3: U$1.40 (SWITCH_3), U$2.40 (SWITCH_3), U$3.40 (SWITCH_3), U$4.40 (SWITCH_3)
SWITCH_4: U$1.41 (SWITCH_4), U$2.41 (SWITCH_4), U$3.41 (SWITCH_4), U$4.41 (SWITCH_4)
SWITCH_5: U$1.42 (SWITCH_5), U$2.42 (SWITCH_5), U$3.42 (SWITCH_5), U$4.42 (SWITCH_5)

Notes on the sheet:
Underwater Robotics Team Ohio State University
Electrical Team
Battery Balancer Connector
ESC Connector
Coprocessor Connector
Actuator Connector
Switch Connector
Robot I2C Connector
Depth Sensor Connector
Test Pin Connector
Board Connected Indicators
Acoustics Connector

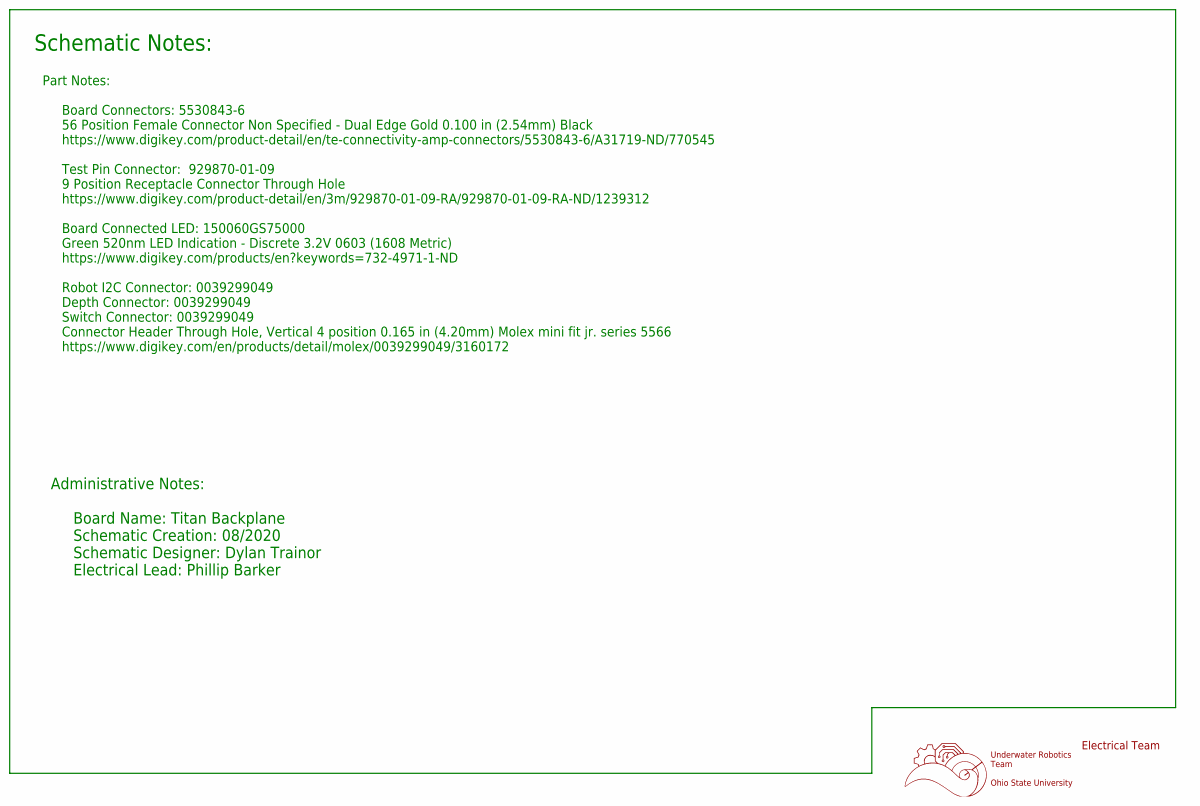
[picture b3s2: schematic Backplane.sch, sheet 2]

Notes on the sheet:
Underwater Robotics Team Ohio State University
Electrical Team
Schematic Notes:
Part Notes: Board Connectors: 5530843-6 56 Position Female Connector Non Specified - Dual Edge Gold 0.100 in (2.54mm) Black https://www.digikey.com/product-detail/en/te-connectivity-amp-connectors/5530843-6/A31719-ND/770545 Test Pin Connector: 929870-01-09 9 Position Receptacle Connector Through Ho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
Administrative Notes: Board Name: Titan Backplane Schematic Creation: 08/2020 Schematic Designer: Dylan Trainor Electrical Lead: Phillip Barker

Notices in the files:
parts and their libraries:
con-molex-mini-fit: Copyright (C) 2011, Bob Starr
SparkFun-DiscreteSemi: Licensing: Creative Commons ShareAlike 4.0 International - https://creativecommons.org/licenses/by-sa/4.0
COPYRIGHT: Copyright (C) 2018 Accelerated Designs. All rights reserved
